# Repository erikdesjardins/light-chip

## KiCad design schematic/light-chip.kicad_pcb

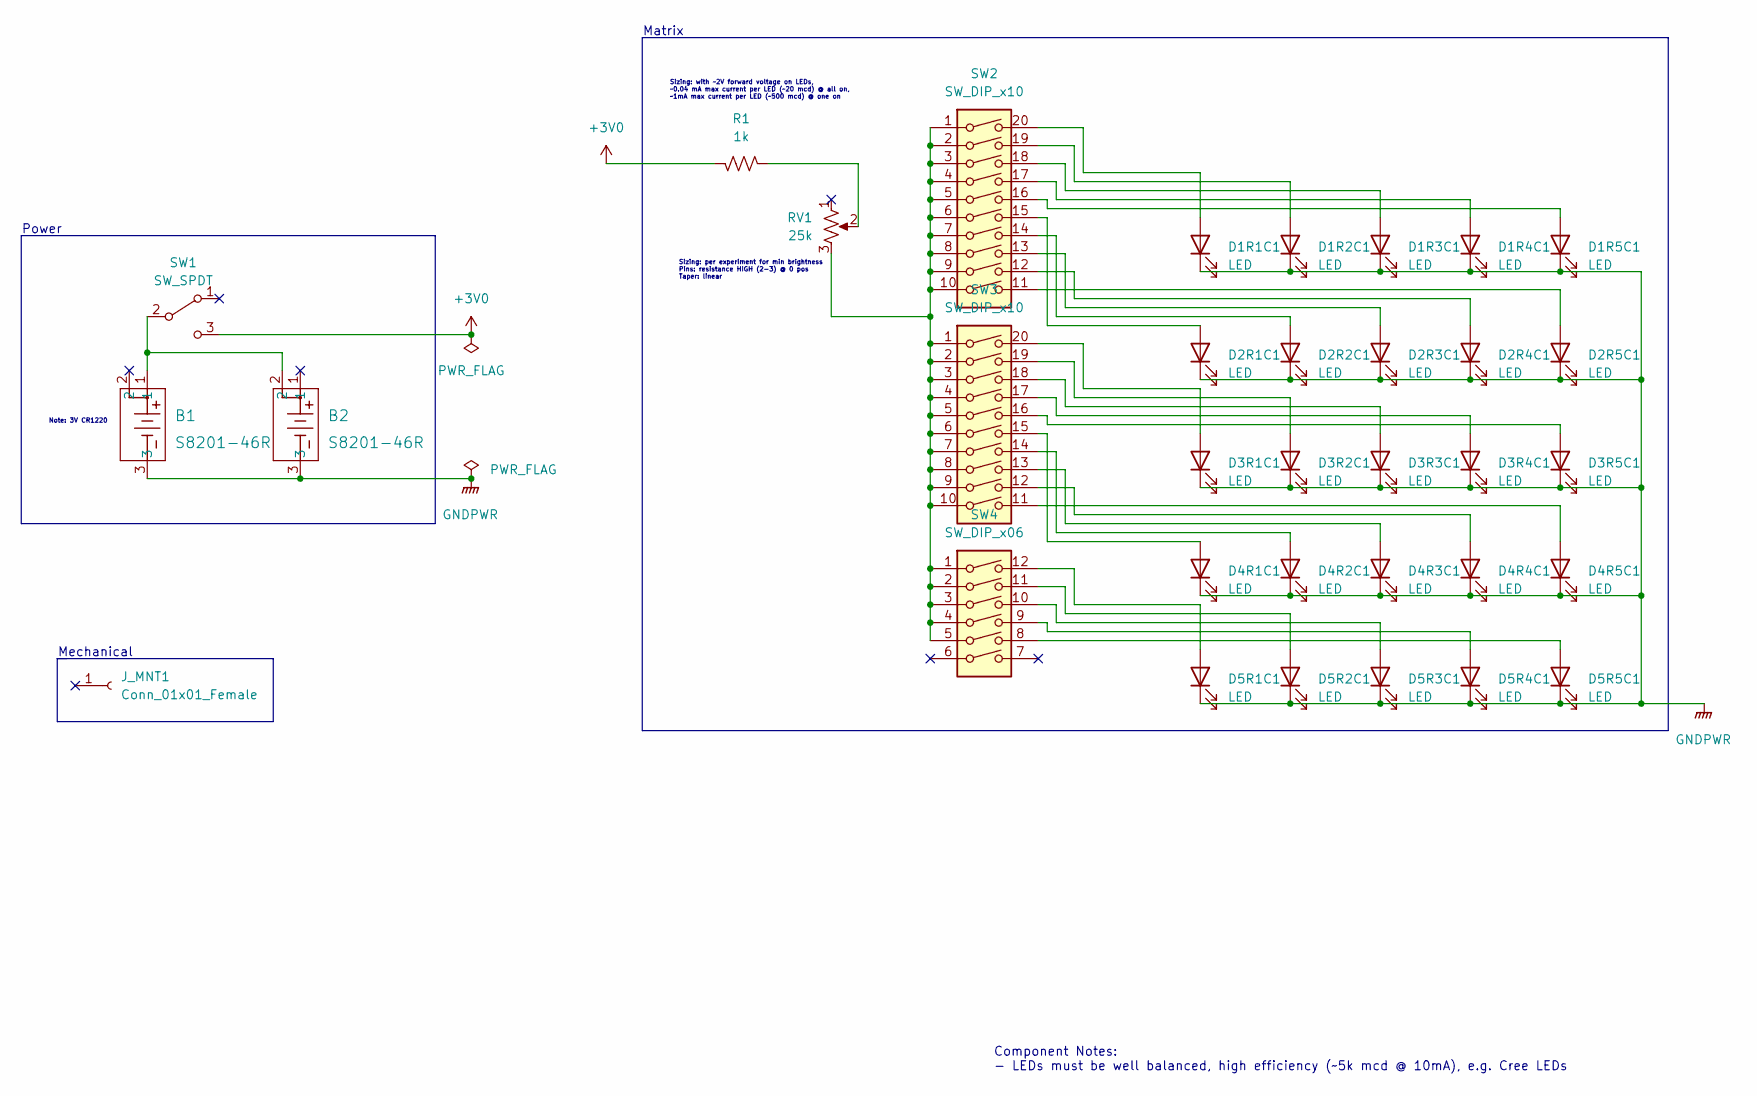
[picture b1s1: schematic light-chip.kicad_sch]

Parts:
B1, B2: S8201-46R; S8201-46R_HRW
D1R1C1, D1R2C1, D1R3C1, D1R4C1, D1R5C1, D2R1C1, D2R2C1, D2R3C1, D2R4C1, D2R5C1, D3R1C1, D3R2C1, D3R3C1, D3R4C1, D3R5C1, D4R1C1, D4R2C1, D4R3C1, D4R4C1, D4R5C1, D5R1C1, D5R2C1, D5R3C1, D5R4C1, D5R5C1: LED; LED_D5.0mm
J_MNT1: Conn_01x01_Female; MountingHole_3.2mm_M3_Pad
R1: 1k; R_Axial_DIN0204_L3.6mm_D1.6mm_P7.62mm_Horizontal
RV1: 25k; RES3_91A_TTE
SW1: SW_SPDT; OS102011MA1Q
SW2, SW3: SW_DIP_x10; SMDIP-20_halfpitch_W7.62mm
SW4: SW_DIP_x06; SMDIP-12_halfpitch_W7.62mm

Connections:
+3V0: R1.1, SW1.3 (C)
GNDPWR: B1.3, B2.3, D1R1C1.1 (K), D1R2C1.1 (K), D1R3C1.1 (K), D1R4C1.1 (K), D1R5C1.1 (K), D2R1C1.1 (K), D2R2C1.1 (K), D2R3C1.1 (K), D2R4C1.1 (K), D2R5C1.1 (K), D3R1C1.1 (K), D3R2C1.1 (K), D3R3C1.1 (K), D3R4C1.1 (K), D3R5C1.1 (K), D4R1C1.1 (K), D4R2C1.1 (K), D4R3C1.1 (K), D4R4C1.1 (K), D4R5C1.1 (K), D5R1C1.1 (K), D5R2C1.1 (K), D5R3C1.1 (K), D5R4C1.1 (K), D5R5C1.1 (K)
unnamed: B1.1, B2.2, SW1.2 (B)
unnamed: D1R1C1.2 (A), SW2.20
unnamed: D1R2C1.2 (A), SW2.19
unnamed: D1R3C1.2 (A), SW2.18
unnamed: D1R4C1.2 (A), SW2.17
unnamed: D1R5C1.2 (A), SW2.16
unnamed: D2R1C1.2 (A), SW2.15
unnamed: D2R2C1.2 (A), SW2.14
unnamed: D2R3C1.2 (A), SW2.13
unnamed: D2R4C1.2 (A), SW2.12
unnamed: D2R5C1.2 (A), SW2.11
unnamed: D3R1C1.2 (A), SW3.20
unnamed: D3R2C1.2 (A), SW3.19
unnamed: D3R3C1.2 (A), SW3.18
unnamed: D3R4C1.2 (A), SW3.17
unnamed: D3R5C1.2 (A), SW3.16
unnamed: D4R1C1.2 (A), SW3.15
unnamed: D4R2C1.2 (A), SW3.14
unnamed: D4R3C1.2 (A), SW3.13
unnamed: D4R4C1.2 (A), SW3.12
unnamed: D4R5C1.2 (A), SW3.11
unnamed: D5R1C1.2 (A), SW4.12
unnamed: D5R2C1.2 (A), SW4.11
unnamed: D5R3C1.2 (A), SW4.10
unnamed: D5R4C1.2 (A), SW4.9
unnamed: D5R5C1.2 (A), SW4.8
unnamed: R1.2, RV1.2
unnamed: RV1.3, SW2.1, SW2.2, SW2.3, SW2.4, SW2.5, SW2.6, SW2.7, SW2.8, SW2.9, SW2.10, SW3.1, SW3.2, SW3.3, SW3.4, SW3.5, SW3.6, SW3.7, SW3.8, SW3.9, SW3.10, SW4.1, SW4.2, SW4.3, SW4.4, SW4.5

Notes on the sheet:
Note: 3V CR1220
Sizing: with ~2V forward voltage on LEDs, ~0.04 mA max current per LED (~20 mcd) @ all on, ~1mA max current per LED (~500 mcd) @ one on
Power
Mechanical
Matrix
Sizing: per experiment for min brightness Pins: resistance HIGH (2-3) @ 0 pos Taper: linear
Component Notes: - LEDs must be well balanced, high efficiency (~5k mcd @ 10mA), e.g. Cree LEDs

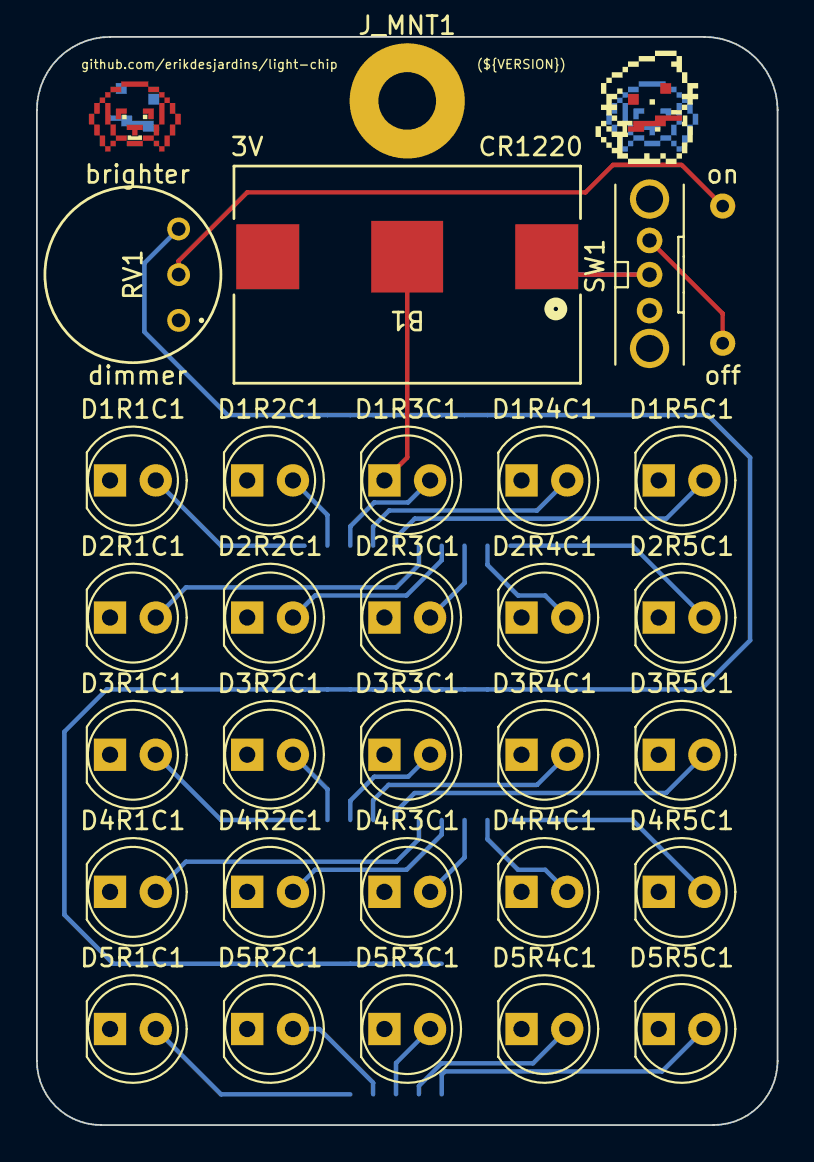
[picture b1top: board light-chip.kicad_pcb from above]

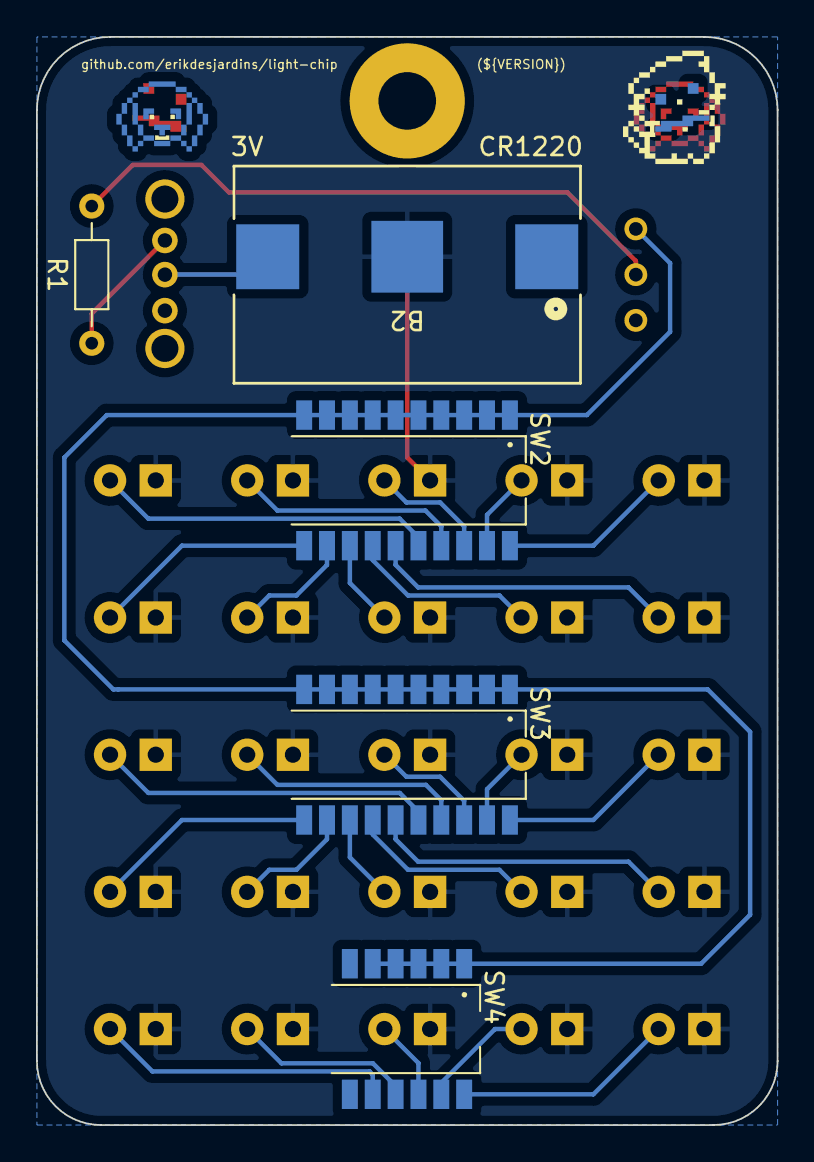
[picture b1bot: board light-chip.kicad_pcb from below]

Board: 2 copper layers, 41.1 x 60.5 mm, 34 parts (5 on the bottom side), 30 nets.

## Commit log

2023-10-09 add autosaved files to gitignore
2023-10-09 init schematic
2023-10-09 add footprints
2023-10-09 add missing switch schematic
2023-10-09 add second battery
2023-10-09 add mechanical component for mounting hole
2023-10-09 init pcb layout
2023-10-09 initial completed pcb
2023-10-09 tweak layouts for better routing, add text labels on controls
2023-10-09 add text labels for battery
2023-10-09 add version text and constant
2023-10-09 add pixel art
2023-10-09 fix silkscreen clipped by solder mask warnings
